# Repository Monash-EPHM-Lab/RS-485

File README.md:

# RS-485
For Integrating RS-485 technology into BoSL

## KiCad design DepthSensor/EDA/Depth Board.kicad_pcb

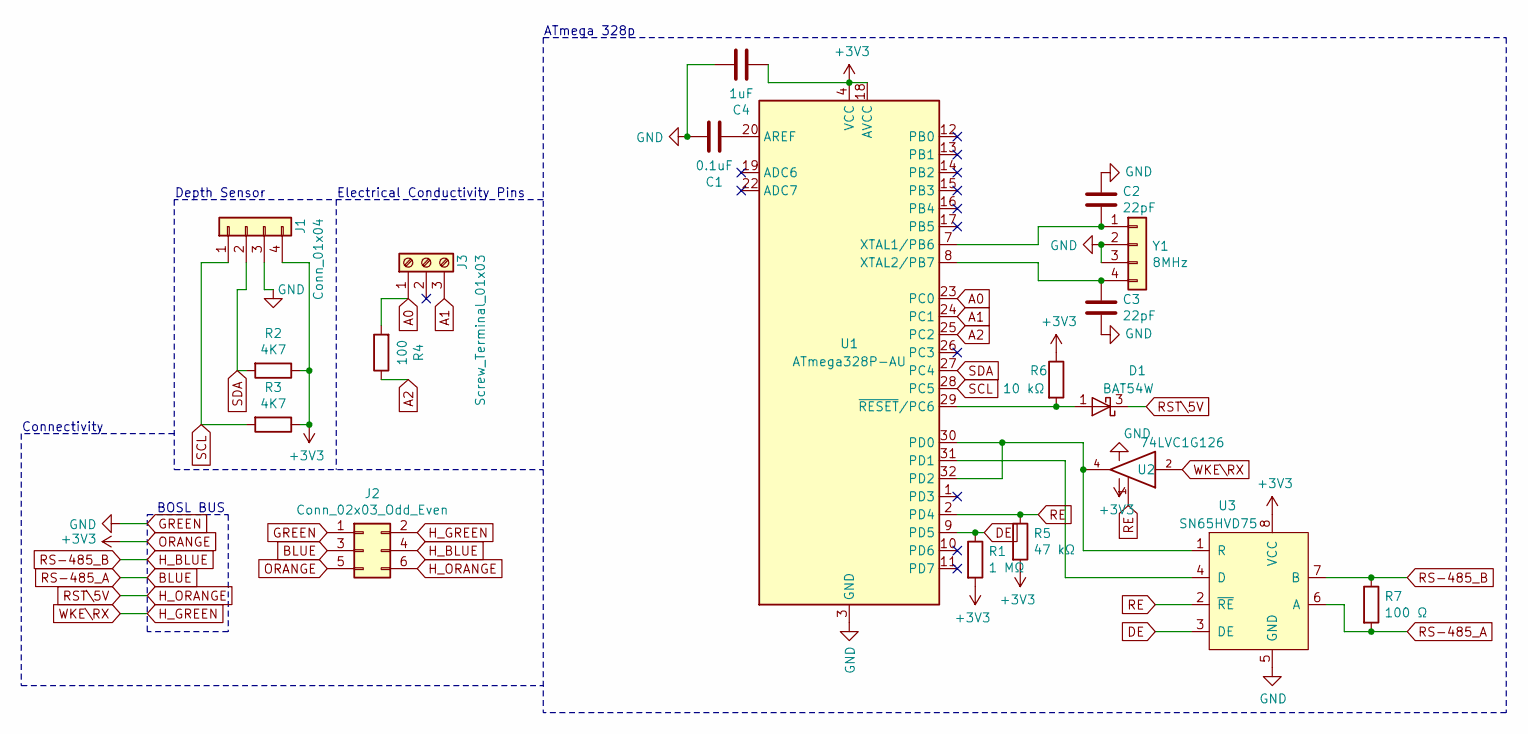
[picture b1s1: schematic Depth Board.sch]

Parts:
C1: 0.1uF; C_0805_2012Metric
C2, C3: 22pF; C_0805_2012Metric
C4: 1uF; C_0805_2012Metric
D1: BAT54W; SOT-323_SC-70
J1: Conn_01x04; Depth_Sensor
J2: Conn_02x03_Odd_Even; PinHeader_2x03_P2.54mm_Vertical
J3: Screw_Terminal_01x03; 3-Pin_ScrewTerminal
R1: 1 MΩ; R_0603_1608Metric
R2, R3: 4K7; R_0805_2012Metric_Pad1.15x1.40mm_HandSolder
R4: 100; R_0805_2012Metric_Pad1.15x1.40mm_HandSolder
R5: 47 kΩ; R_0603_1608Metric
R6: 10 kΩ; R_0805_2012Metric
R7: 100 Ω; R_0805_2012Metric
U1: ATmega328P-AU; TQFP-32_7x7mm_P0.8mm
U2: 74LVC1G126; SOT-353_SC-70-5
U3: SN65HVD75; SOIC-8_3.9x4.9mm_P1.27mm
Y1: 8MHz; Ralton_Crystal

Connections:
A0: J3.1, R4.2, U1.23 (PC0)
A1: J3.3, U1.24 (PC1)
A2: R4.1, U1.25 (PC2)
BLUE: J2.3, R7.2, U3.6 (A)
DE: R1.1, U1.9 (PD5), U3.3 (DE)
GREEN: C1.2, C2.1, C3.2, C4.2, J1.3, J2.1, U1.3 (GND), U1.5 (GND), U1.21 (GND), U2.3 (GND), U3.5 (GND), Y1.2, Y1.3
H_BLUE: J2.4, R7.1, U3.7 (B)
H_GREEN: J2.2, U2.2
H_ORANGE: D1.3 (K), J2.6
unnamed: C1.1, U1.20 (AREF)
unnamed: C2.2, U1.7 (XTAL1/PB6), Y1.1
unnamed: C3.1, U1.8 (XTAL2/PB7), Y1.4
unnamed: D1.1 (A), R6.2, U1.29 (~RESET~/PC6)
unnamed: U1.30 (PD0), U1.32 (PD2), U2.4, U3.1 (R)
unnamed: U1.31 (PD1), U3.4 (D)
ORANGE: C4.1, J1.4, J2.5, R1.2, R2.1, R3.1, R5.2, R6.1, U1.4 (VCC), U1.6 (VCC), U1.18 (AVCC), U2.5 (VCC), U3.8 (VCC)
RE: R5.1, U1.2 (PD4), U2.1, U3.2 (~RE)
SCL: J1.1, R3.2, U1.28 (PC5)
SDA: J1.2, R2.2, U1.27 (PC4)

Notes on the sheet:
Depth Sensor
Electrical Conductivity Pins
BOSL BUS
Connectivity
ATmega 328p

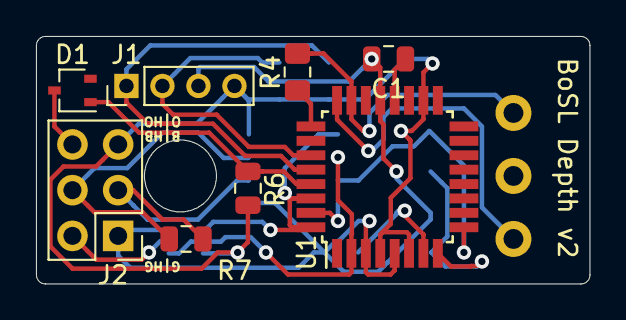
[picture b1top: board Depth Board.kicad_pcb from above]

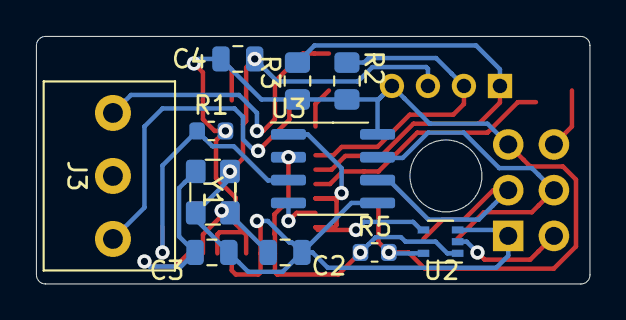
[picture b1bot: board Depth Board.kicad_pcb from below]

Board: 2 copper layers, 30.8 x 13.8 mm, 19 parts (11 on the bottom side), 19 nets.

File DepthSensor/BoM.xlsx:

Part # | Manufacturer | Manufacturer Part # | Designator | Qty | Description | Case | Location | Price | Generic Component | Link
1 | Microchip Technology | ATMEGA328P-AU | U1 | 1 | Microcontroller IC 8-Bit 20MHz 32KB | TQFP | Top | 3.33 | No | https://www.digikey.com.au/product-detail/en/microchip-techn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
2 | Molex | 393570003 | J3 | 1 | 3-Position 3.5mm PCB Screw Terminal | THT | Bottom | 2.59 | No | https://www.digikey.com.au/products/en?keywords=393570003
3 | Ralton | RH100-8.000-8-2020-TR | Y1 | 1 | 8MHz 8pF Crystal | SMD | Bottom | 1.38 | No | https://www.digikey.com.au/product-detail/en/raltron-electro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
4 | Xian Sensors |  | J1 | 1 | SMP 3011 - 35G | THT | Bottom |  | No
5 |  |  | C1 | 1 | Capacitor 0.1uF 0805 | SMD | Bottom | 0.1 | Yes
6 |  |  | C2, C3 | 2 | Capacitor 22pF0805 | SMD | Top | 0.1 | Yes
7 |  |  | C4 | 1 | Capacitor 1uF 0805 | SMD | Bottom | 0.1 | Yes
8 |  |  | R6 | 1 | Resistor 10k ohm 1% 0805 | SMD | Bottom | 0.1 | Yes
9 |  |  | R2, R3 | 2 | Resistor 4k7 ohm 5% 0805 | SMD | Bottom | 0.1 | Yes
10 |  |  | R4, R7 | 2 | Resistor 100 ohm 1%0805 | SMD | Bottom | 0.1 | Yes
 |  |  | R1 | 1 | Resistor 1M ohm 1% 0603
 |  |  | R5 | 1 | Resistor 47K ohm 1% 0603
11 | Nexperia | BAT54W,115 | D1 | 1 | Schottky Diode BAT54W | SOT-323 |  | 0.1 | No | https://au.element14.com/nexperia/bat54w-115/diode-schottky-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
 | Nexperia | 74LVC1G126GW | U2 | 1 | Tri State Buffer | SOT-353 |  | 0.3 | No | https://au.element14.com/nexperia/74lvc1g126gw/ic-logic-74lv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
 | Texas Instruments | SN65HVD75DR | U3 | 1 | RS-485 Line Driver | SOIC-8 |  | 3.77 | No | https://au.mouser.com/ProductDetail/Texas-Instruments/SN65HV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

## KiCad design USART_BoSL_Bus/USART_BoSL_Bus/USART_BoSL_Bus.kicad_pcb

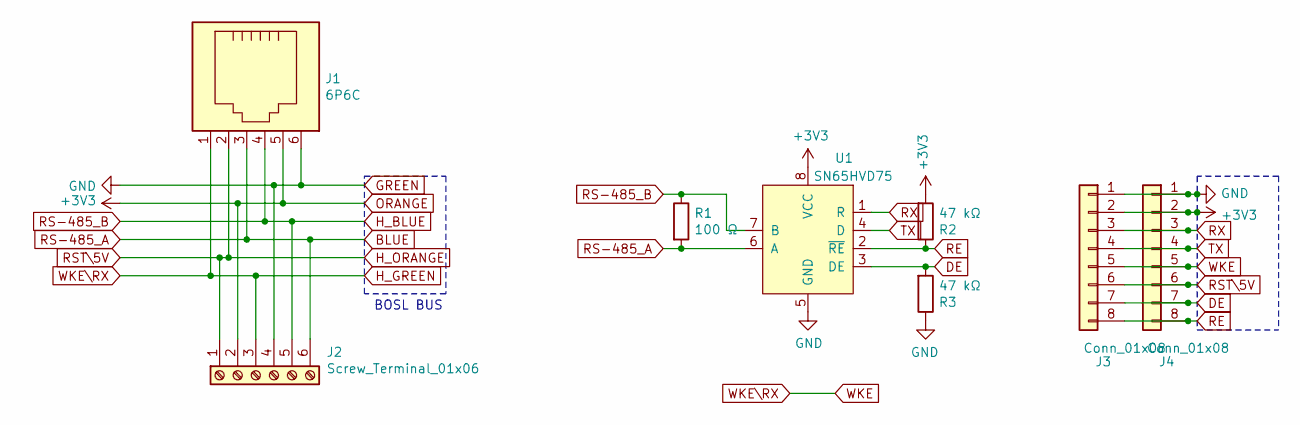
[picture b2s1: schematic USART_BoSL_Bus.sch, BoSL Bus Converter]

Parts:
J1: 6P6C; RJ12_Amphenol_54601
J2: Screw_Terminal_01x06; TerminalBlock_Phoenix_PT-1,5-6-3.5-H_1x06_P3.50mm_Horizontal
J3: Conn_01x08; PinSocket_1x08_P2.54mm_Vertical
J4: Conn_01x08; PinHeader_1x08_P2.54mm_Vertical
R1: 100 Ω; R_0603_1608Metric
R2, R3: 47 kΩ; R_0603_1608Metric
U1: SN65HVD75; SOIC-8_3.9x4.9mm_P1.27mm

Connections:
BLUE: J1.3, J2.6, R1.2, U1.6 (A)
DE: J3.7, J4.7, R3.2, U1.3 (DE)
GREEN: J1.6, J2.4, J3.1, J4.1, R3.1, U1.5 (GND)
H_BLUE: J1.4, J2.5, R1.1, U1.7 (B)
H_GREEN: J1.1, J2.3, J3.5, J4.5
H_ORANGE: J1.2, J2.1, J3.6, J4.6
ORANGE: J1.5, J2.2, J3.2, J4.2, R2.2, U1.8 (VCC)
RE: J3.8, J4.8, R2.1, U1.2 (~RE)
RX: J3.3, J4.3, U1.1 (R)
TX: J3.4, J4.4, U1.4 (D)

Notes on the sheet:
BOSL BUS

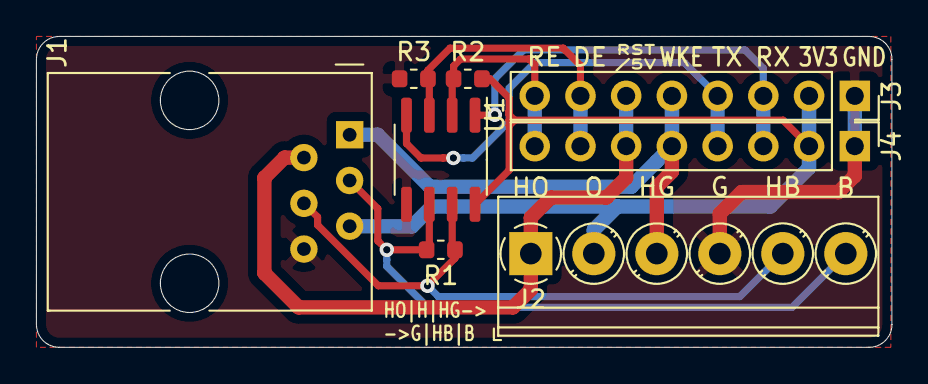
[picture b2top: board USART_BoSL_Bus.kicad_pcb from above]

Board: 2 copper layers, 47.5 x 17.3 mm, 8 parts (0 on the bottom side), 10 nets.

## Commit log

2020-07-06 added concept schematic
2020-07-07 began ading implemtation of bosl_bus on atmega328p
2020-07-08 daily commit
2020-07-08 added schematic for USART-BoSLBus interconnector
2020-07-09 added BOM for interconnect added layout for interconnect
2020-07-21 added nonname files before fix
2020-07-21 added usart bosl bus schematic and pcb
2020-07-21 added BOM for USART BOSL converter
2020-07-22 added RS-485 to depth sensor
2020-07-22 added production files fro bosl bus converter
2020-08-06 added rev 0.1.1 of bosl bus converter, replaced pin headers for screw terminasl and hanging wires
2020-09-11 added implementation of RS485 library
2020-09-14 added test versions for velocity sensor code
2020-09-16 working rs485 code
2020-09-16 added files for universal library
2020-09-18 annotated library file
2020-09-29 finished RS485 library
2020-11-18 added documentation for depth sensor schematics
